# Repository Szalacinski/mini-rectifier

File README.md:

# mini-rectifier
50V 8A rectifier board with screw terminals

Most of the caps on the Chinese boards aren't rated to the voltages I needed, so I made this.

Use capacitor_board for reduced ripple current at higher amperages.

If a heatsink is needed, the rectifier can be mounted on the bottom, folded over, and screwed to a heatsink.

If operating at higher voltages, be sure to add an appropriate bleeder resistor.

Output ready for JLCPCB

## BOM

| Part | Qty |
| ---- | --- |
| [WJ500V-5.08-2P](https://lcsc.com/product-detail/Screw-terminal_Ningbo-Kangnex-Elec-WJ500V-5-08-2P_C8465.html) | 2 |
| [GBU8005](https://lcsc.com/product-detail/Bridge-Rectifiers_Shandong-Jingdao-Microelectronics-GBU8005_C438424.html) | 1 |
| [UVY1H332MHD](https://www.digikey.com/en/products/detail/UVY1H332MHD/493-12473-ND/2539663) | 1 |

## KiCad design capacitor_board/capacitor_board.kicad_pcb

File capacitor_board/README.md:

# Rectifier Capacitor Board
Capacitor board for reducing ripple current at 8A

## BOM

| Part | Qty |
| ---- | --- |
| [WJ500V-5.08-2P](https://lcsc.com/product-detail/Screw-terminal_Ningbo-Kangnex-Elec-WJ500V-5-08-2P_C8465.html) | 2 |
| [‎50USC10000MEFCSN25X50‎](https://www.digikey.com/en/products/detail/50USC10000MEFCSN25X50/1189-2739-ND/3565438) | 3 |
| [ECA-1HM222‎](https://www.digikey.com/en/products/detail/ECA-1HM222/P5187-ND/245046) | 1 |
| [ FMP100JR-52-4K7 ](https://www.digikey.com/en/products/detail/yageo/FMP100JR-52-4K7/2058612) | 1 |

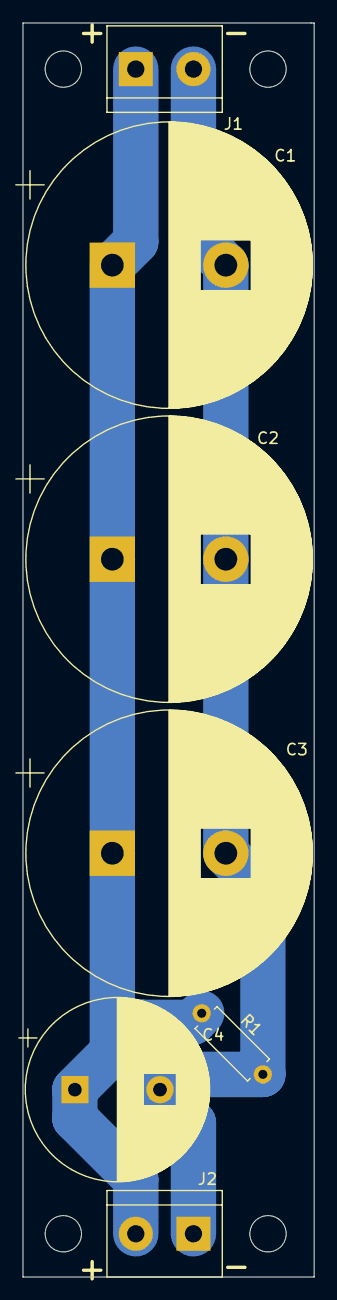
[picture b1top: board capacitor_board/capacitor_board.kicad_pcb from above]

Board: 2 copper layers, 25.7 x 110.5 mm, 11 parts (0 on the bottom side), 2 nets.

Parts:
C1, C2, C3: CP; CP_Radial_D25.0mm_P10.00mm_SnapIn
C4: CP; CP_Radial_D16.0mm_P7.50mm
H1, H2, H3, H4: MountingHole; MountingHole_3.2mm_M3
J1, J2: Screw_Terminal_01x02; TerminalBlock_bornier-2_P5.08mm
R1: R; R_Axial_DIN0207_L6.3mm_D2.5mm_P7.62mm_Horizontal

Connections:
unnamed: C1.1, C2.1, C3.1, C4.1, J1.1, J2.2, R1.1
unnamed: C1.2, C2.2, C3.2, C4.2, J1.2, J2.1, R1.2

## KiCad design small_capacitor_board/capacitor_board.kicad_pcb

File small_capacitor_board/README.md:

# Rectifier Small Capacitor Board
Small capacitor board for reducing ripple current at 4A

## BOM

| Part | Qty |
| ---- | --- |
| [WJ500V-5.08-2P](https://lcsc.com/product-detail/Screw-terminal_Ningbo-Kangnex-Elec-WJ500V-5-08-2P_C8465.html) | 2 |
| [‎50USC10000MEFCSN25X50‎](https://www.digikey.com/en/products/detail/50USC10000MEFCSN25X50/1189-2739-ND/3565438) | 1 |
| [ FMP100JR-52-4K7 ](https://www.digikey.com/en/products/detail/yageo/FMP100JR-52-4K7/2058612) | 1 |

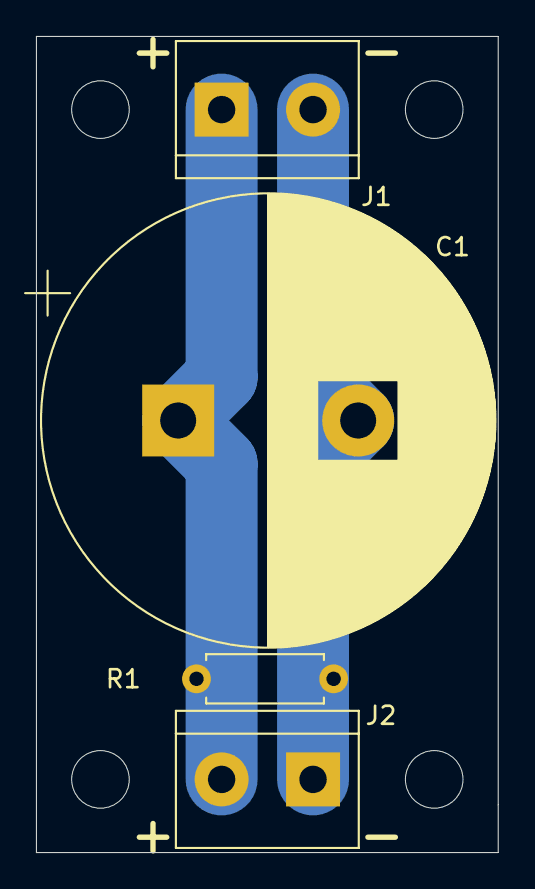
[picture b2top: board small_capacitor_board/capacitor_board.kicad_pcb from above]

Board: 2 copper layers, 25.7 x 45.3 mm, 8 parts (0 on the bottom side), 2 nets.

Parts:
C1: CP; CP_Radial_D25.0mm_P10.00mm_SnapIn
H1, H2, H3, H4: MountingHole; MountingHole_3.2mm_M3
J1, J2: Screw_Terminal_01x02; TerminalBlock_bornier-2_P5.08mm
R1: R; R_Axial_DIN0207_L6.3mm_D2.5mm_P7.62mm_Horizontal

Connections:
unnamed: C1.1, J1.1, J2.2, R1.1
unnamed: C1.2, J1.2, J2.1, R1.2

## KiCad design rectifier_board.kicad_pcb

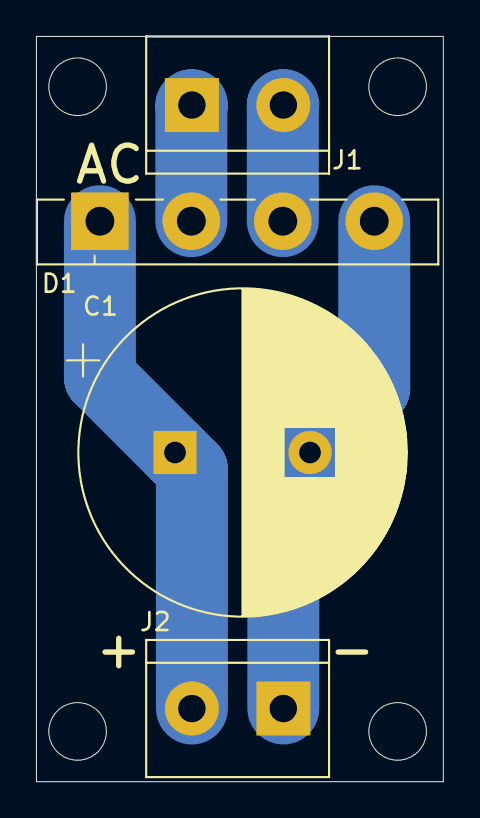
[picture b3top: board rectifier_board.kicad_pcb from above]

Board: 2 copper layers, 22.6 x 41.4 mm, 8 parts (0 on the bottom side), 4 nets.

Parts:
C1: CP; CP_Radial_D18.0mm_P7.50mm
D1: GBU8B; Diode_Bridge_Vishay_GBU
H1, H2, H3, H4: MountingHole; MountingHole_3.2mm_M3
J1, J2: Screw_Terminal_01x02; TerminalBlock_bornier-2_P5.08mm

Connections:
unnamed: C1.1, D1.1, J2.2
unnamed: C1.2, D1.4, J2.1
unnamed: D1.2, J1.1
unnamed: D1.3, J1.2
